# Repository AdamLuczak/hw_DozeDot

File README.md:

# DozeDot

## Overview
The *DozeDot* is a compact and versatile module featuring the ATTiny816 microcontroller, powered by a CR2032 battery. This board is designed with power efficiency in mind, primarily operating in a sleep mode and waking up to perform specific tasks. It includes RX/TX serial ports, an I2C bus, and two pins for touch detection. The board also features two user LEDs (userLED and sysLED), a transistor-based buzzer control circuit for piezoelectric buzzers, and can be externally powered apart from its built-in CR battery.

The ATTiny816 at the heart of DozeDot offers 8 KB of Flash memory, 512 bytes of SRAM, and 128 bytes of EEPROM, making it capable of handling a variety of tasks while maintaining low power consumption. Its 20 MHz maximum clock speed ensures responsive performance in applications requiring quick wake-up and processing.

## Design Details

### PCB Layout
- **Top View**: 
  
- **Bottom View**: 

### Schematic
- **Schematic Diagram**:

### Physical Board Images
### Physical Board Images

## License
The *DozeDot* project is made available under the MIT License, which means you are free to use, modify, and distribute it in both private and commercial applications.

- **Permission to Use**: You are free to use, modify, and distribute this design in both private and commercial settings.
- **Attribution Requirement**: While not required, attribution to the original author, Adam Łuczak, is appreciated. This can be done through a citation or a link back to this repository.
- **No Warranty**: This design is provided "as is", without warranty of any kind. Use it at your own risk.
- **Liability**: The author is not liable for any damages or losses that may arise from the use of this design.

For the full terms and conditions, please refer to the MIT License documentation.

## Contact
For any inquiries or suggestions about the *Drzemiąca Kropka* project, please feel free to contact Adam Łuczak at adam.luczak@outlook.com

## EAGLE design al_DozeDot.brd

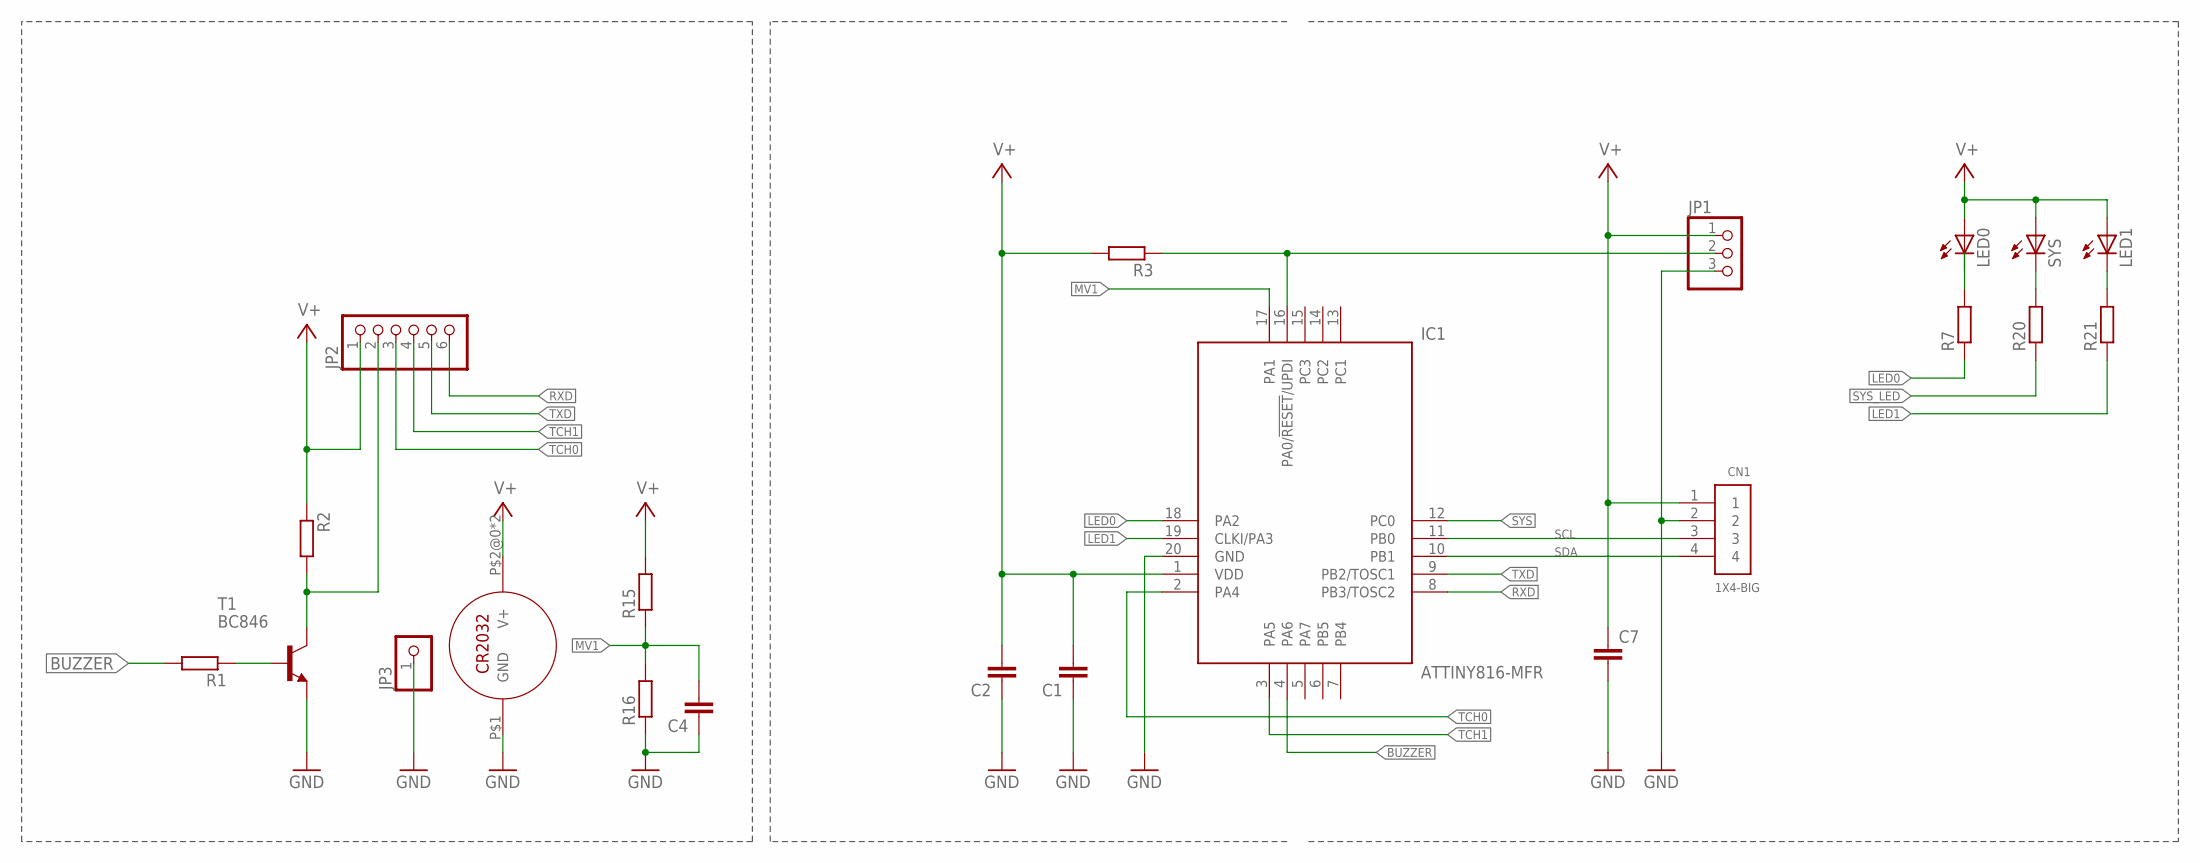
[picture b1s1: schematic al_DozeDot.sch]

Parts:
C1, C2, C4: C-EUC0603; C0603
C7: C-EUC0603K; C0603K
CN1: 1X4-BIG; 1X04-BIG
IC1: ATTINY816-MFR; SOIC127P1030X265-20N
JP1: PINHD-1X3; 1X03
JP2: PINHD-1X6; 1X06
JP3: PINHD-1X1; 1X01
LED0, LED1: LED_ESML0603; LED_SML0603
R1, R2: RR0603; R0603
R3, R7, R15, R16, R20, R21: R-EU_R0603; R0603
SYS: LED_ESML0603; LED_SML0603
T1: BC846; SOT23
U$2: CR2032; DS1092-07-W6L

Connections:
BUZZER: IC1.4 (PA6), R1.2
GND: C1.1, C2.1, C4.1, C7.2, CN1.2, IC1.20 (GND), JP1.3, JP3.1, R16.1, T1.2 (E), U$2.P$1 (GND)
LED0: IC1.18 (PA2), R7.1
LED1: IC1.19 (CLKI/PA3), R21.1
MV1: C4.2, IC1.17 (PA1), R15.1, R16.2
unnamed: R1.1, T1.1 (B)
unnamed: JP2.2, R2.2, T1.3 (C)
unnamed: IC1.16 (PA0/!RESET!/UPDI), JP1.2, R3.1
unnamed: LED0.C, R7.2
unnamed: LED1.C, R21.2
unnamed: R20.2, SYS.C
RXD: IC1.8 (PB3/TOSC2), JP2.6
SCL: CN1.3, IC1.11 (PB0)
SDA: CN1.4, IC1.10 (PB1)
SYS: IC1.12 (PC0)
SYS_LED: R20.1
TCH0: IC1.2 (PA4), JP2.3
TCH1: IC1.3 (PA5), JP2.4
TXD: IC1.9 (PB2/TOSC1), JP2.5
V+: C1.2, C2.2, C7.1, CN1.1, IC1.1 (VDD), JP1.1, JP2.1, LED0.A, LED1.A, R2.1, R3.2, R15.2, SYS.A, U$2.P$2@0 (V+), U$2.P$2@1 (V+)

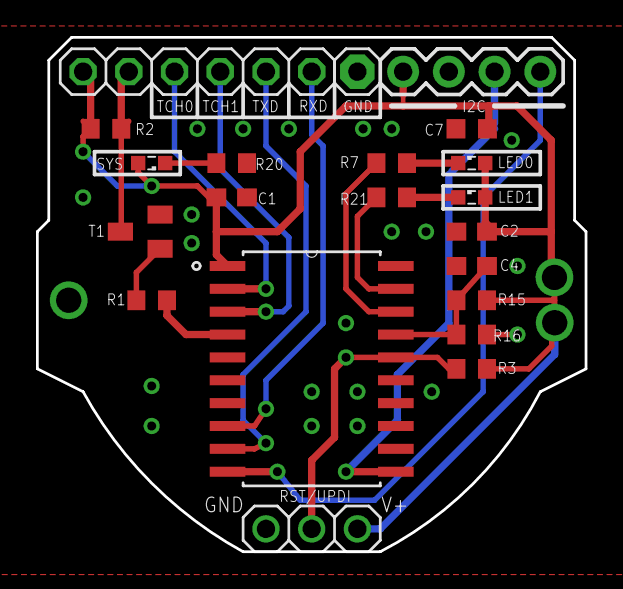
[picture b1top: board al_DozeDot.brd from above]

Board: 2 copper layers, 30.5 x 28.6 mm, 22 parts (1 on the bottom side), 18 nets.

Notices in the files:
README.md:
License: MIT
